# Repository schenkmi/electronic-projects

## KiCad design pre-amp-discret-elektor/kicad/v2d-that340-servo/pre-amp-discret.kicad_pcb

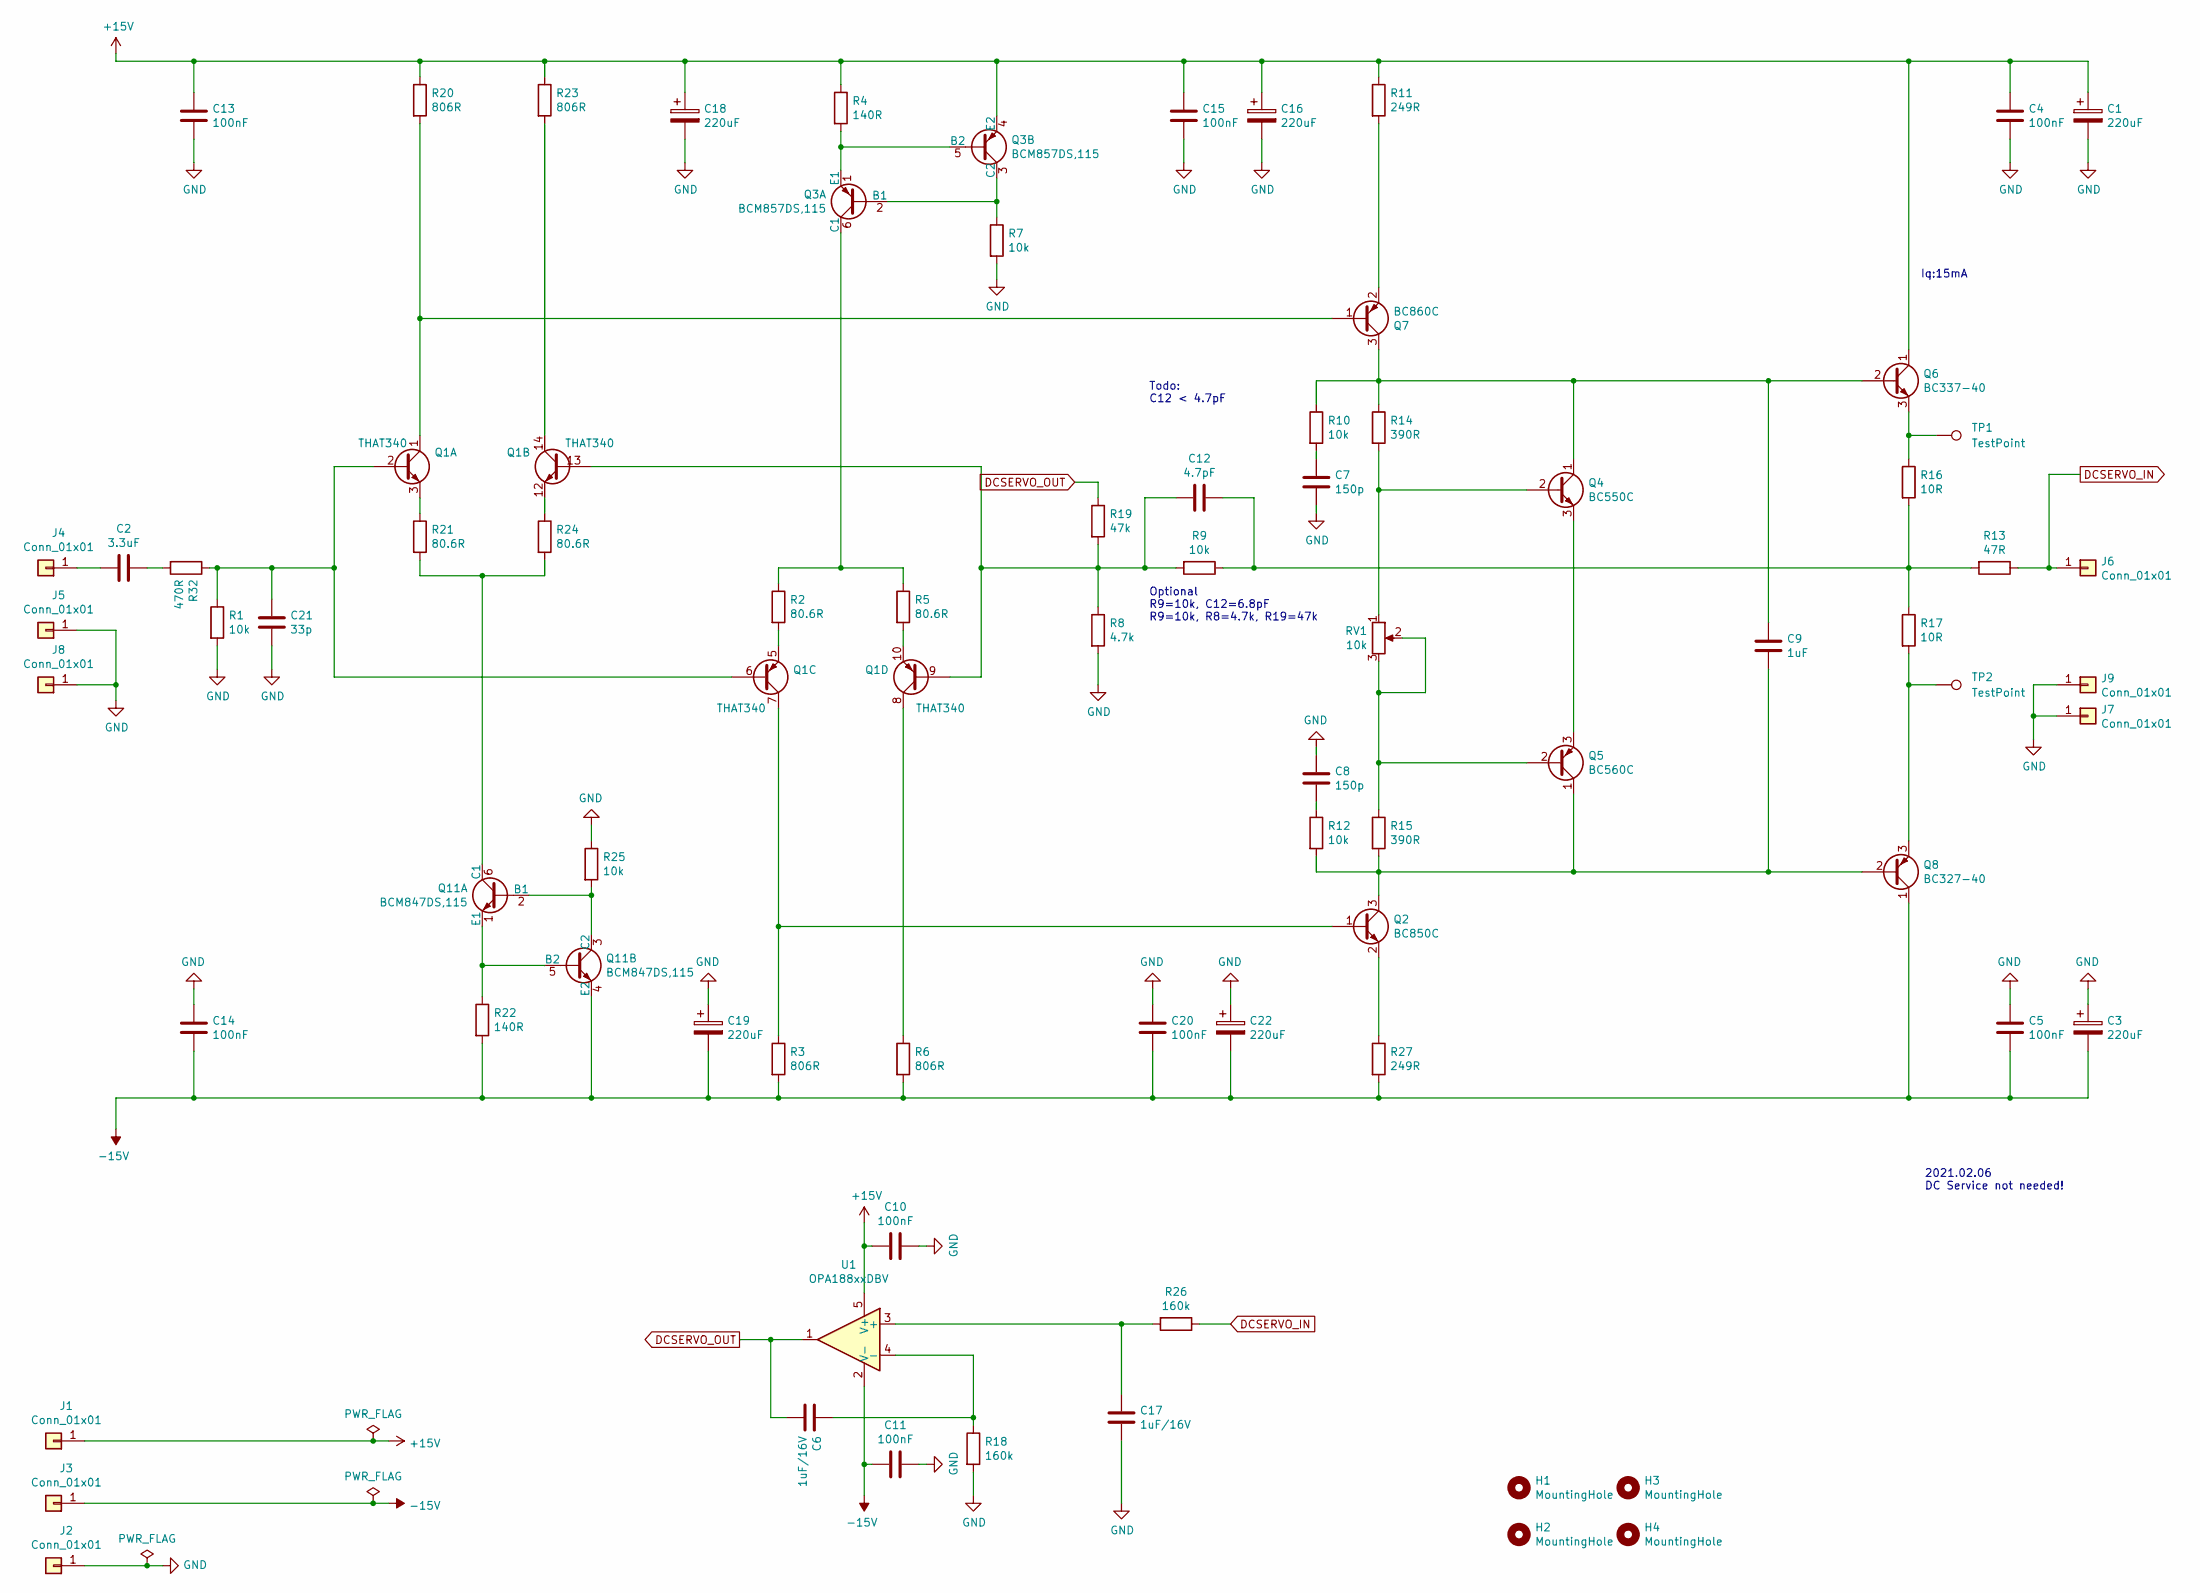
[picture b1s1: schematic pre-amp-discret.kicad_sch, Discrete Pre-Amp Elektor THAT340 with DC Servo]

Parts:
C1, C3, C16, C18, C19, C22: 220uF; CP_Radial_D8.0mm_P3.50mm
C2: 3.3uF; C_Rect_L7.2mm_W7.2mm_P5.00mm_FKS2_FKP2_MKS2_MKP2
C4, C5, C13, C14, C15, C20: 100nF; C_1210_3225Metric_Pad1.33x2.70mm_HandSolder
C6, C17: 1uF/16V; C_1210_3225Metric_Pad1.33x2.70mm_HandSolder
C7, C8: 150p; C_0805_2012Metric_Pad1.18x1.45mm_HandSolder
C9: 1uF; C_Rect_L7.2mm_W5.5mm_P5.00mm_FKS2_FKP2_MKS2_MKP2
C10, C11: 100nF; C_0603_1608Metric_Pad1.08x0.95mm_HandSolder
C12: 4.7pF; C_0805_2012Metric_Pad1.18x1.45mm_HandSolder
C21: 33p; C_0805_2012Metric_Pad1.18x1.45mm_HandSolder
H1, H2, H3, H4: MountingHole; MountingHole_3.2mm_M3
J1, J2, J3, J4, J5, J6, J7, J8, J9: Conn_01x01; Pin_D1.0mm_L10.0mm
Q1: THAT340
Q2: BC850C; SOT-23
Q3: BCM857DS,115; SC-74-6_1.5x2.9mm_P0.95mm
Q4: BC550C; TO-92_Inline
Q5: BC560C; TO-92_Inline
Q6: BC337-40; TO-92_Inline
Q7: BC860C; SOT-23
Q8: BC327-40; TO-92_Inline
Q11: BCM847DS,115; SC-74-6_1.5x2.9mm_P0.95mm
R1, R7, R9, R10, R12, R25: 10k; R_0805_2012Metric_Pad1.20x1.40mm_HandSolder
R2, R5, R21, R24: 80.6R; R_0805_2012Metric_Pad1.20x1.40mm_HandSolder
R3, R6, R20, R23: 806R; R_0805_2012Metric_Pad1.20x1.40mm_HandSolder
R4, R22: 140R; R_0805_2012Metric_Pad1.20x1.40mm_HandSolder
R8: 4.7k; R_0805_2012Metric_Pad1.20x1.40mm_HandSolder
R11, R27: 249R; R_0805_2012Metric_Pad1.20x1.40mm_HandSolder
R13: 47R; R_0805_2012Metric_Pad1.20x1.40mm_HandSolder
R14, R15: 390R; R_0805_2012Metric_Pad1.20x1.40mm_HandSolder
R16, R17: 10R; R_0805_2012Metric_Pad1.20x1.40mm_HandSolder
R18, R26: 160k; R_0805_2012Metric_Pad1.20x1.40mm_HandSolder
R19: 47k; R_0805_2012Metric_Pad1.20x1.40mm_HandSolder
R32: 470R; R_0805_2012Metric_Pad1.20x1.40mm_HandSolder
RV1: 10k; Potentiometer_Bourns_3296W_Vertical
TP1, TP2: TestPoint; TestPoint_Pad_D1.0mm
U1: OPA188xxDBV; TSOT-23-5

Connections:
+15V: C1.1, C4.2, C10.2, C13.2, C15.2, C16.1, C18.1, J1.1, Q3.4 (E2), Q6.1 (C), R4.1, R11.1, R20.1, R23.1, U1.5 (V+)
-15V: C3.2, C5.1, C11.2, C14.1, C19.2, C20.1, C22.2, J3.1, Q8.1 (C), Q11.4 (E2), R3.2, R6.2, R22.2, R27.2, U1.2 (V-)
DCSERVO_IN: J6.1, R13.1, R26.1
DCSERVO_OUT: C6.1, R19.1, U1.1
GND: C1.2, C3.1, C4.1, C5.2, C7.1, C8.2, C10.1, C11.1, C13.1, C14.2, C15.1, C16.2, C17.1, C18.2, C19.1, C20.2, C21.1, C22.1, J2.1, J5.1, J7.1, J8.1, J9.1, R1.2, R7.2, R8.2, R18.2, R25.1
unnamed: C2.1, R32.2
unnamed: C2.2, J4.1
unnamed: C6.2, R18.1, U1.4 (-)
unnamed: C7.2, R10.2
unnamed: C8.1, R12.1
unnamed: C9.1, Q2.3 (C), Q5.1 (C), Q8.2 (B), R12.2, R15.2
unnamed: C9.2, Q4.1 (C), Q6.2 (B), Q7.3 (C), R10.1, R14.1
unnamed: C12.1, R9.1, R13.2, R16.2, R17.1
unnamed: C12.2, Q1.9 (B), Q1.13 (B), R8.1, R9.2, R19.2
unnamed: C17.2, R26.2, U1.3 (+)
unnamed: C21.2, Q1.2 (B), Q1.6 (B), R1.1, R32.1
unnamed: Q1.7 (E), Q2.1 (B), R3.1
unnamed: Q2.2 (E), R27.1
unnamed: Q3.1 (E1), Q3.5 (B2), R4.2
unnamed: Q3.2 (B1), Q3.3 (C2), R7.1
unnamed: Q3.6 (C1), R2.1, R5.1
unnamed: Q4.2 (B), R14.2, RV1.1
unnamed: Q4.3 (E), Q5.3 (E)
unnamed: Q5.2 (B), R15.1, RV1.2, RV1.3
unnamed: Q6.3 (E), R16.1, TP1.1
unnamed: Q1.1 (C), Q7.1 (B), R20.2
unnamed: Q7.2 (E), R11.2
unnamed: Q8.3 (E), R17.2, TP2.1
unnamed: Q11.1 (E1), Q11.5 (B2), R22.1
unnamed: Q11.2 (B1), Q11.3 (C2), R25.2
unnamed: Q11.6 (C1), R21.2, R24.2
unnamed: Q1.5 (C), R2.2
unnamed: Q1.10, R5.2
unnamed: Q1.8 (E), R6.1
unnamed: Q1.3 (E), R21.1
unnamed: Q1.14 (C), R23.2
unnamed: Q1.12 (E), R24.1

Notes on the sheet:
2021.02.06 DC Service not needed!
Optional R9=10k, C12=6.8pF R9=10k, R8=4.7k, R19=47k
Todo: C12 < 4.7pF
Iq:15mA

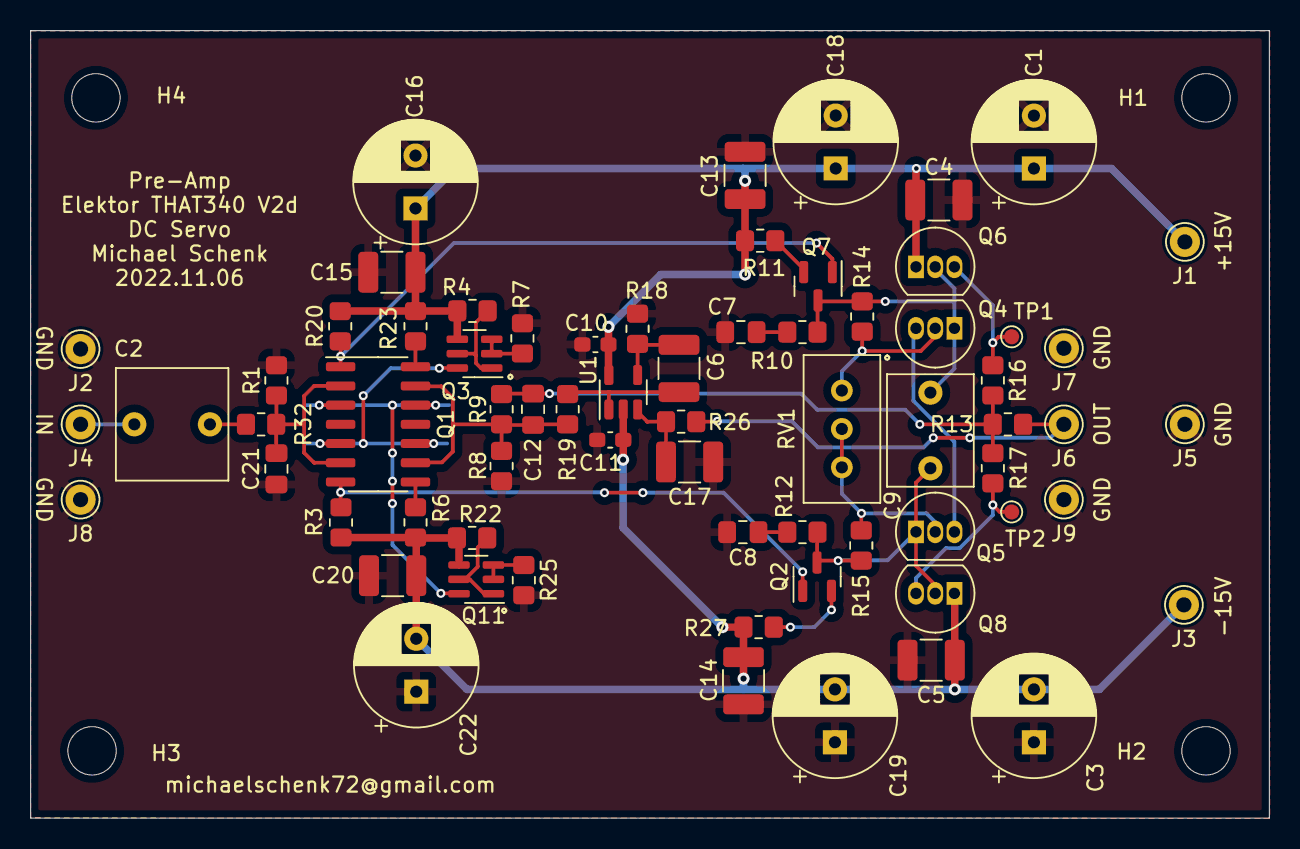
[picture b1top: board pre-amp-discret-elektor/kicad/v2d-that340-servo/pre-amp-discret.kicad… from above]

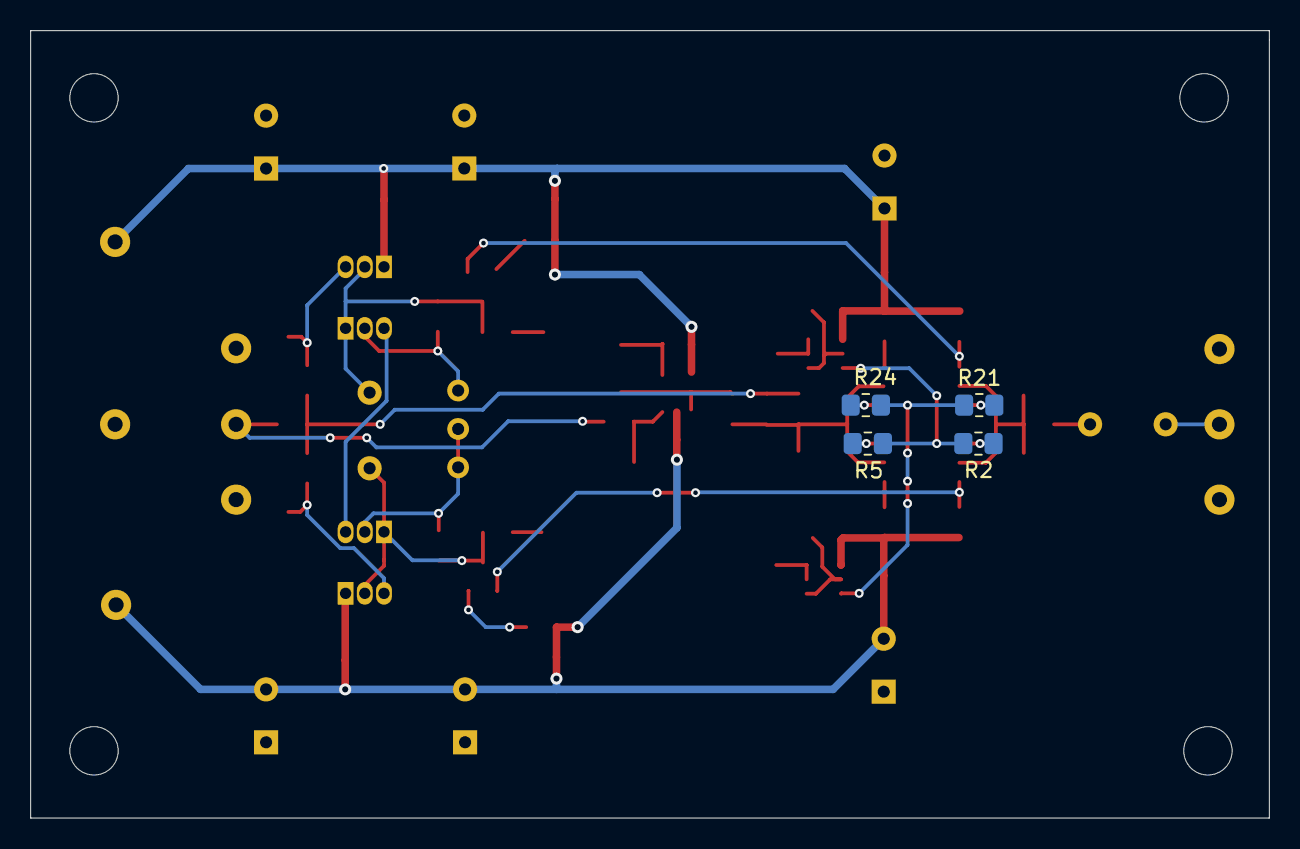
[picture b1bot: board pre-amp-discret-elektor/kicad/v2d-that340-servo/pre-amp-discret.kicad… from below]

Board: 2 copper layers, 81.9 x 52.1 mm, 76 parts (4 on the bottom side), 37 nets.

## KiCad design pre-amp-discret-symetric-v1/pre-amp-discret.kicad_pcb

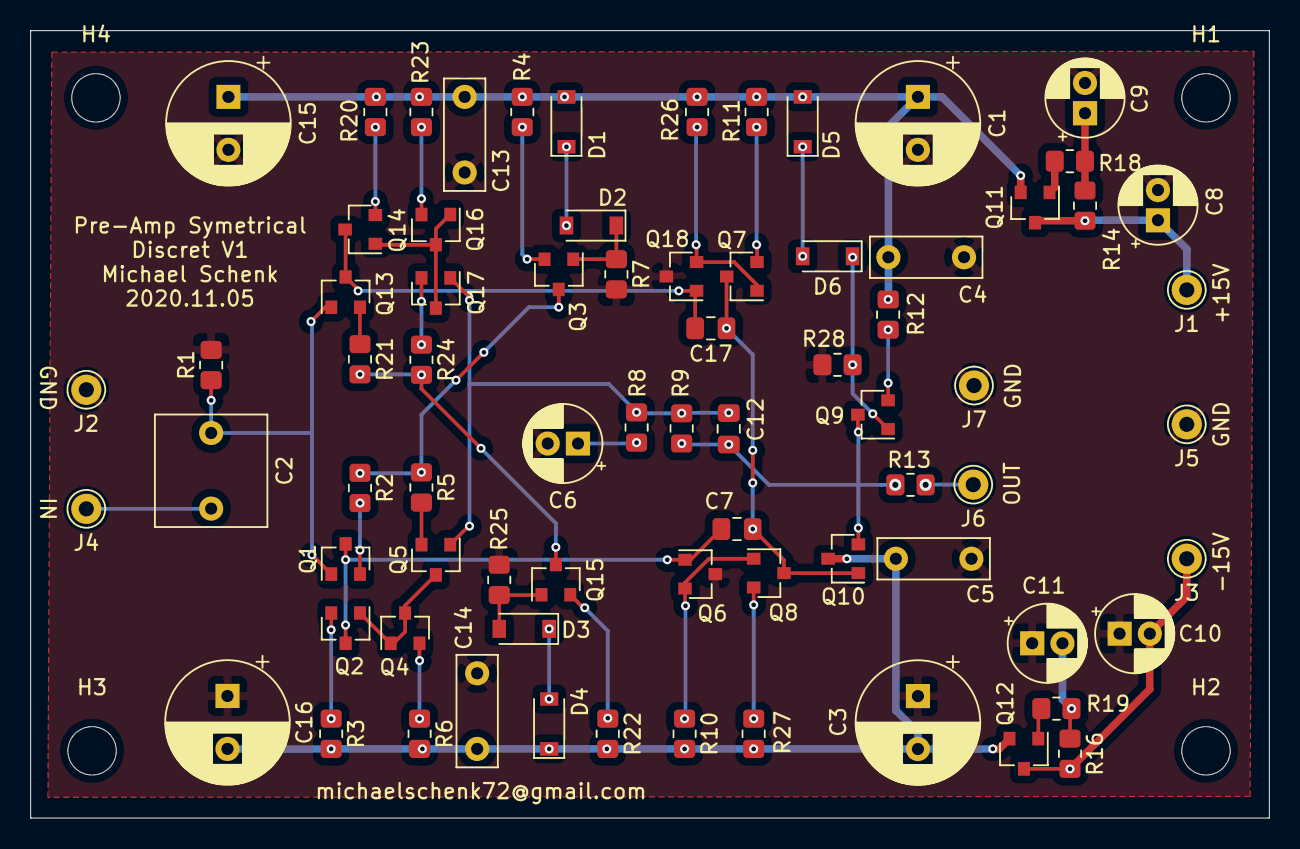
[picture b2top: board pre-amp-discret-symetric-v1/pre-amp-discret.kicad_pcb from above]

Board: 2 copper layers, 81.9 x 52.1 mm, 78 parts (0 on the bottom side), 43 nets.

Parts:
C1, C3, C15, C16: 220uF; CP_Radial_D8.0mm_P3.50mm
C2: 2.2uF; C_Rect_L7.2mm_W7.2mm_P5.00mm_FKS2_FKP2_MKS2_MKP2
C4, C5, C13, C14: 100nF; C_Rect_L7.2mm_W2.5mm_P5.00mm_FKS2_FKP2_MKS2_MKP2
C6, C8, C9, C10, C11: 100uF; CP_Radial_D5.0mm_P2.00mm
C7, C17: 270pF; C_0805_2012Metric_Pad1.18x1.45mm_HandSolder
C12: 4.7pF; C_0805_2012Metric_Pad1.18x1.45mm_HandSolder
D1, D2, D3, D4, D5, D6: 1N4148W; D_SOD-123
H1, H2, H3, H4: MountingHole; MountingHole_3.2mm_M3
J1, J2, J3, J4, J5, J6, J7: Conn_01x01; Pin_D1.0mm_L10.0mm
Q1, Q3, Q5, Q7, Q9, Q10, Q12, Q14, Q16, Q18: BC860C; SOT-23
Q2, Q4, Q6, Q8, Q11, Q13, Q15, Q17: BC850C; SOT-23
R1, R8, R9: 22k; R_0805_2012Metric_Pad1.20x1.40mm_HandSolder
R2, R5, R12, R18, R19, R21, R24: 100R; R_0805_2012Metric_Pad1.20x1.40mm_HandSolder
R3, R6, R20, R23: 68R; R_0805_2012Metric_Pad1.20x1.40mm_HandSolder
R4, R22: 220R; R_0805_2012Metric_Pad1.20x1.40mm_HandSolder
R7, R14, R16, R25, R28: 10k; R_0805_2012Metric_Pad1.20x1.40mm_HandSolder
R10, R26: 2k2; R_0805_2012Metric_Pad1.20x1.40mm_HandSolder
R11, R27: 39R; R_0805_2012Metric_Pad1.20x1.40mm_HandSolder
R13: 47R; R_0805_2012Metric_Pad1.20x1.40mm_HandSolder

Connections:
+15V: C1.1, C4.2, C13.2, C15.1, D1.2, D5.2, Q11.2, R4.1, R11.1, R12.1, R20.1, R23.1, R26.1
-15V: C3.2, C5.1, C14.1, C16.2, D4.1, Q10.3, Q12.2, R3.2, R6.2, R10.2, R22.2, R27.2
GND: C1.2, C3.1, C4.1, C5.2, C6.2, C8.2, C9.2, C10.1, C11.1, C13.1, C14.2, C15.2, C16.1, J2.1, J5.1, J7.1, Q6.3, Q18.3, R1.2, R7.2, R25.1, R28.2
unnamed: C2.1, Q1.1, Q13.1, R1.1
unnamed: C2.2, J4.1
unnamed: C6.1, R8.2
unnamed: C7.2, Q1.3, Q2.3, Q6.1
unnamed: C8.1, J1.1, Q11.3, R14.2
unnamed: C9.1, R14.1, R18.1
unnamed: C10.2, J3.1, Q12.3, R16.2
unnamed: C11.2, R16.1, R19.1
unnamed: C12.1, Q9.3, Q10.2, R9.1, R13.2
unnamed: C12.2, Q5.1, Q17.1, R8.1, R9.2
unnamed: C7.1, C17.1, Q7.3, Q8.3, Q10.1
unnamed: C17.2, Q13.3, Q14.3, Q18.1
unnamed: D1.1, D2.2
unnamed: D2.1, Q3.1, R7.1
unnamed: D3.1, D4.2
unnamed: D3.2, Q15.1, R25.2
unnamed: D5.1, D6.2
unnamed: D6.1, Q9.1, R28.1
unnamed: J6.1, R13.1
unnamed: Q1.2, R2.2
unnamed: Q2.1, Q4.1, Q4.3, Q5.3
unnamed: Q2.2, R3.1
unnamed: Q3.2, R4.2
unnamed: Q3.3, R2.1, R5.1
unnamed: Q4.2, R6.1
unnamed: Q5.2, R5.2
unnamed: Q6.2, Q8.1, R10.1
unnamed: Q7.2, R11.2
unnamed: Q8.2, R27.1
unnamed: Q9.2, R12.2
unnamed: Q11.1, R18.2
unnamed: Q12.1, R19.2
unnamed: Q13.2, R21.1
unnamed: Q14.1, Q16.1, Q16.3, Q17.3
unnamed: Q14.2, R20.2
unnamed: Q15.2, R22.1
unnamed: Q15.3, R21.2, R24.2
unnamed: Q16.2, R23.2
unnamed: Q17.2, R24.1
unnamed: Q7.1, Q18.2, R26.2
